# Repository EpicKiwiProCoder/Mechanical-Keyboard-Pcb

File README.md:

A 3d printed mechanical keyboard with a fully custom designed Pcb. It's a 60% keyboard which means that it has fewer keys than a regular keyboard, but who uses the pause break anyway?
I have fully built it and it's working fantastically.

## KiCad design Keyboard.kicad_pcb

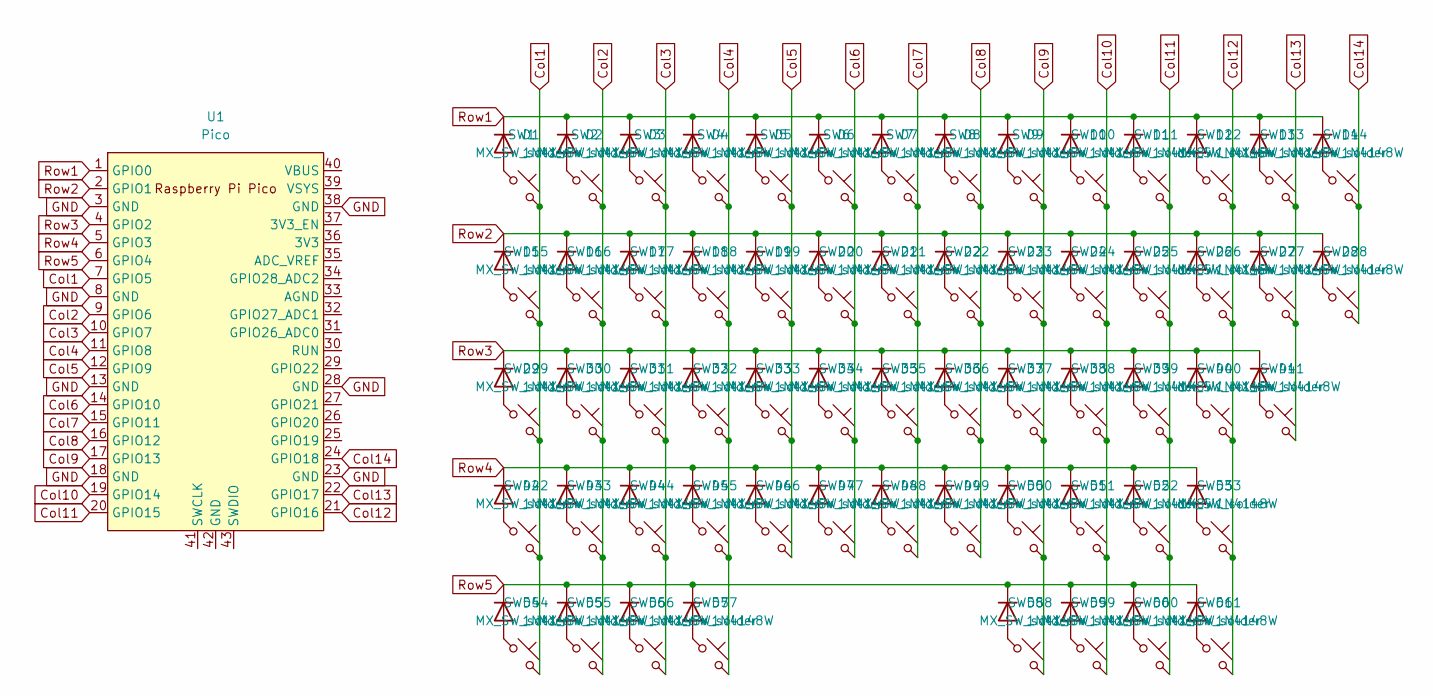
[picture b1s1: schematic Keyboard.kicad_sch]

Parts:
D1, D2, D3, D4, D5, D6, D7, D8, D9, D10, D11, D12, D13, D14, D15, D16, D17, D18, D19, D20, D21, D22, D23, D24, D25, D26, D27, D28, D29, D30, D31, D32, D33, D34, D35, D36, D37, D38, D39, D40, D41, D42, D43, D44, D45, D46, D47, D48, D49, D50, D51, D52, D53, D54, D55, D56, D57, D58, D59, D60, D61: 1N4148W; D_SOD-123
SW1, SW2, SW3, SW4, SW5, SW6, SW7, SW8, SW9, SW10, SW11, SW12, SW13, SW14, SW16, SW17, SW18, SW19, SW20, SW21, SW22, SW23, SW24, SW25, SW26, SW27, SW30, SW31, SW32, SW33, SW34, SW35, SW36, SW37, SW38, SW39, SW40, SW41, SW42, SW43, SW44, SW45, SW46, SW47, SW48, SW49, SW50, SW51, SW52, SW53, SW57: MX_SW_solder; SW_MX_1u
SW15, SW28: MX_SW_solder; SW_MX_1.5u
SW29: MX_SW_solder; SW_MX_1.75u
SW54, SW55, SW56, SW58, SW59, SW60, SW61: MX_SW_solder; SW_MX_1.25u
U1: Pico; RPi_Pico_SMD_TH

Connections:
Col1: SW1.2, SW15.2, SW29.2, SW42.2, SW54.2, U1.7 (GPIO5)
Col2: SW2.2, SW16.2, SW30.2, SW43.2, SW55.2, U1.9 (GPIO6)
Col3: SW3.2, SW17.2, SW31.2, SW44.2, SW56.2, U1.10 (GPIO7)
Col4: SW4.2, SW18.2, SW32.2, SW45.2, SW57.2, U1.11 (GPIO8)
Col5: SW5.2, SW19.2, SW33.2, SW46.2, U1.12 (GPIO9)
Col6: SW6.2, SW20.2, SW34.2, SW47.2, U1.14 (GPIO10)
Col7: SW7.2, SW21.2, SW35.2, SW48.2, U1.15 (GPIO11)
Col8: SW8.2, SW22.2, SW36.2, SW49.2, U1.16 (GPIO12)
Col9: SW9.2, SW23.2, SW37.2, SW50.2, SW58.2, U1.17 (GPIO13)
Col10: SW10.2, SW24.2, SW38.2, SW51.2, SW59.2, U1.19 (GPIO14)
Col11: SW11.2, SW25.2, SW39.2, SW52.2, SW60.2, U1.20 (GPIO15)
Col12: SW12.2, SW26.2, SW40.2, SW53.2, SW61.2, U1.21 (GPIO16)
Col13: SW13.2, SW27.2, SW41.2, U1.22 (GPIO17)
Col14: SW14.2, SW28.2, U1.24 (GPIO18)
GND: U1.3 (GND), U1.8 (GND), U1.13 (GND), U1.18 (GND), U1.23 (GND), U1.28 (GND), U1.38 (GND)
unnamed: D1.2 (A), SW1.1
unnamed: D2.2 (A), SW2.1
unnamed: D3.2 (A), SW3.1
unnamed: D4.2 (A), SW4.1
unnamed: D5.2 (A), SW5.1
unnamed: D6.2 (A), SW6.1
unnamed: D7.2 (A), SW7.1
unnamed: D8.2 (A), SW8.1
unnamed: D9.2 (A), SW9.1
unnamed: D10.2 (A), SW10.1
unnamed: D11.2 (A), SW11.1
unnamed: D12.2 (A), SW12.1
unnamed: D13.2 (A), SW13.1
unnamed: D14.2 (A), SW14.1
unnamed: D15.2 (A), SW15.1
unnamed: D16.2 (A), SW16.1
unnamed: D17.2 (A), SW17.1
unnamed: D18.2 (A), SW18.1
unnamed: D19.2 (A), SW19.1
unnamed: D20.2 (A), SW20.1
unnamed: D21.2 (A), SW21.1
unnamed: D22.2 (A), SW22.1
unnamed: D23.2 (A), SW23.1
unnamed: D24.2 (A), SW24.1
unnamed: D25.2 (A), SW25.1
unnamed: D26.2 (A), SW26.1
unnamed: D27.2 (A), SW27.1
unnamed: D28.2 (A), SW28.1
unnamed: D29.2 (A), SW29.1
unnamed: D30.2 (A), SW30.1
unnamed: D31.2 (A), SW31.1
unnamed: D32.2 (A), SW32.1
unnamed: D33.2 (A), SW33.1
unnamed: D34.2 (A), SW34.1
unnamed: D35.2 (A), SW35.1
unnamed: D36.2 (A), SW36.1
unnamed: D37.2 (A), SW37.1
unnamed: D38.2 (A), SW38.1
unnamed: D39.2 (A), SW39.1
unnamed: D40.2 (A), SW40.1
unnamed: D41.2 (A), SW41.1
unnamed: D42.2 (A), SW42.1
unnamed: D43.2 (A), SW43.1
unnamed: D44.2 (A), SW44.1
unnamed: D45.2 (A), SW45.1
unnamed: D46.2 (A), SW46.1
unnamed: D47.2 (A), SW47.1
unnamed: D48.2 (A), SW48.1
unnamed: D49.2 (A), SW49.1
unnamed: D50.2 (A), SW50.1
unnamed: D51.2 (A), SW51.1
unnamed: D52.2 (A), SW52.1
unnamed: D53.2 (A), SW53.1
unnamed: D54.2 (A), SW54.1
unnamed: D55.2 (A), SW55.1
unnamed: D56.2 (A), SW56.1
unnamed: D57.2 (A), SW57.1
unnamed: D58.2 (A), SW58.1
unnamed: D59.2 (A), SW59.1
unnamed: D60.2 (A), SW60.1
unnamed: D61.2 (A), SW61.1
Row1: D1.1 (K), D2.1 (K), D3.1 (K), D4.1 (K), D5.1 (K), D6.1 (K), D7.1 (K), D8.1 (K), D9.1 (K), D10.1 (K), D11.1 (K), D12.1 (K), D13.1 (K), D14.1 (K), U1.1 (GPIO0)
Row2: D15.1 (K), D16.1 (K), D17.1 (K), D18.1 (K), D19.1 (K), D20.1 (K), D21.1 (K), D22.1 (K), D23.1 (K), D24.1 (K), D25.1 (K), D26.1 (K), D27.1 (K), D28.1 (K), U1.2 (GPIO1)
Row3: D29.1 (K), D30.1 (K), D31.1 (K), D32.1 (K), D33.1 (K), D34.1 (K), D35.1 (K), D36.1 (K), D37.1 (K), D38.1 (K), D39.1 (K), D40.1 (K), D41.1 (K), U1.4 (GPIO2)
Row4: D42.1 (K), D43.1 (K), D44.1 (K), D45.1 (K), D46.1 (K), D47.1 (K), D48.1 (K), D49.1 (K), D50.1 (K), D51.1 (K), D52.1 (K), D53.1 (K), U1.5 (GPIO3)
Row5: D54.1 (K), D55.1 (K), D56.1 (K), D57.1 (K), D58.1 (K), D59.1 (K), D60.1 (K), D61.1 (K), U1.6 (GPIO4)

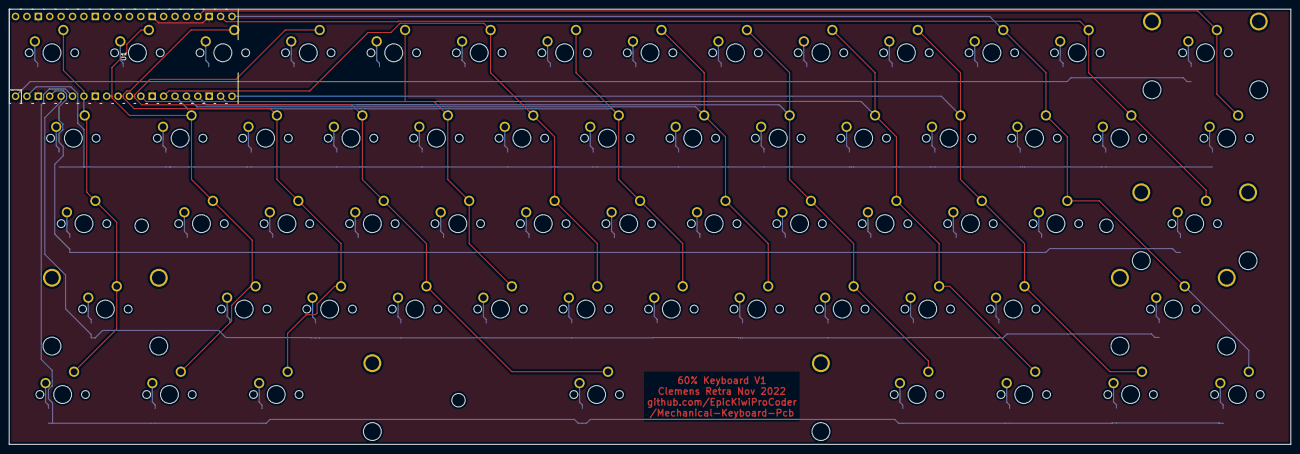
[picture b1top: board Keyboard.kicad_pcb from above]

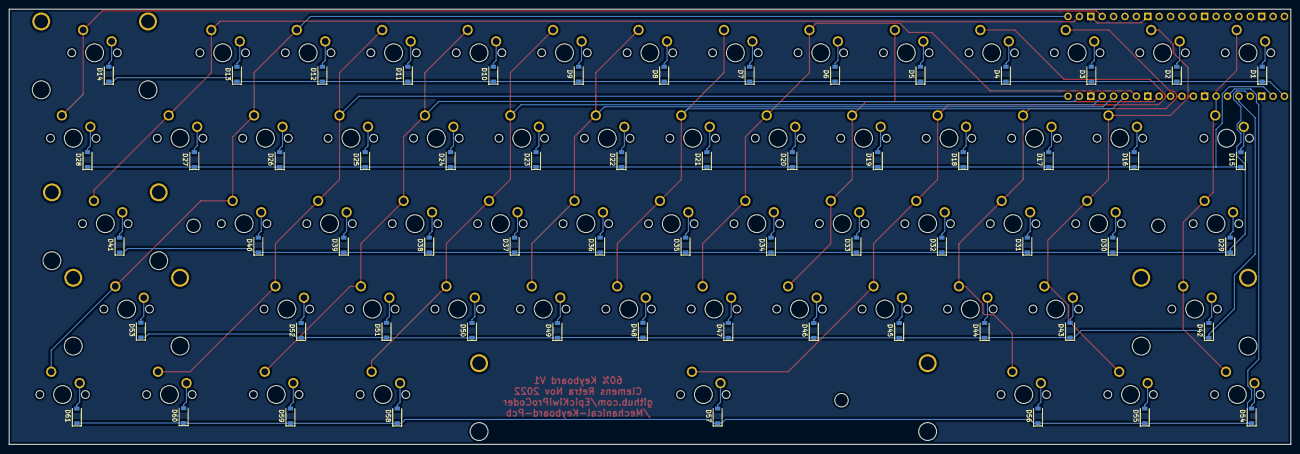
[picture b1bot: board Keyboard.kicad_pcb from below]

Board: 2 copper layers, 285.7 x 97.0 mm, 130 parts (61 on the bottom side), 81 nets.

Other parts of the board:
M1, M2, M3: MountingHole_3.2mm_M3
STAB1: STAB_MX_P_2u
STAB2, STAB3: STAB_MX_P_2.25u
STAB4: STAB_MX_P_2.75u

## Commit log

2022-10-26 60% done
2022-10-26 removed backups
2022-10-26 rerouted with correct pico placement
2022-10-26 removed errors
2022-10-26 Export v1 .grb
2022-10-27 Filled copper layer and added final touches
2022-10-28 Added mounting holes and generated .gbr's
2022-11-04 Added Pcb Art
2022-11-06 Last edits made
2022-11-27 Added 3d Models
